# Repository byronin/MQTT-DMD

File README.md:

# MQTT-DMD for ESP8266

## Contents
- PCB [Hardware](https://github.com/byronin/MQTT-DMD/tree/main/Hardware "Hardware") files prepared for controlling the P10 Display.
- [Arduino library](https://github.com/byronin/MQTT-DMD/tree/main/Lib%26Software "Arduino library")  for using P10 Display with Mqtt.

## Sponsor

#### Thanks to PCBWay for handling PCB production.

## Hardware & BOM

  ##### This PCB Desing with Eagle  
  
  ## Schematic

| PCB Components  | Package |Piece || PCB Components  | Package |Piece |  
| ------------- | ------------- |------------- |---------| ------------- | ------------- |------------- |
| ESP8266 Wi-Fi Module  | 12E | 1 pcs  || LM1117-3v3 | SOT-223  | 1 pcs |
| SS14/SS36 Diode  | DO-214AC | 1 pcs || 3v3 Zener Diode  | SOD80C | 1 pcs |
| MAX485-RS485 | SOP 8  | 1 pcs  || 100uf Cap | PANASONIC_D   | 2 pcs |
| 100nf Cap mlcc | 0603  | 3 pcs || 10K Resistor  | 0603  | 8 pcs  |
| 1K Resistor | 0603  | 2 pcs || 120R Resistor  | 0603  | 2 pcs  |
| RED LED  | 0603  | 1 pcs || BLUE LED  | 0603  | 1 pcs  |
| Screw Terminal  | 3.5mm DIP  | 2 pcs  || Header 2x8 FML | 2.54-180  | 1 pcs  |
| Header 1x4 ML  | 2.54-90  | 1 pcs  || Header 1x2 ML  | 2.54-180  | 2 pcs  |
| JUMPER 1x2   | 2.54  | 2 pcs  |  

[You can look BOM.txt for details.](https://github.com/byronin/MQTT-DMD/blob/main/Hardware/BOM.txt "You can look BOM.txt")  

## Test 

#### Shopping List

| Product  | Link |
| ------------- | ------------- |
|P10 Display|[ Link](https://tr.aliexpress.com/item/1005003237909713.html?spm=a2g0o.productlist.0.0.37e759f1OWtOJo&algo_pvid=ac306e69-5e60-4847-98bb-0beb025dface&algo_exp_id=ac306e69-5e60-4847-98bb-0beb025dface-14&pdp_ext_f=%7B%22sku_id%22%3A%2212000024792668676%22%7D&pdp_npi=2%40dis%21TRY%21%21114.7%21%21%21209.95%21%21%402101d8b516565254069212787e109b%2112000024792668676%21sea " Link")|
| LM2596 |[Link](https://tr.aliexpress.com/item/33004374185.html?spm=a2g0o.productlist.0.0.584a4eb1nGv9CS&algo_pvid=40dddc8f-dfae-4d0d-81c2-a52a0aa0245e&algo_exp_id=40dddc8f-dfae-4d0d-81c2-a52a0aa0245e-0&pdp_ext_f=%7B%22sku_id%22%3A%2267088944738%22%7D&pdp_npi=2%40dis%21TRY%21%2113.03%21%21%2126.97%21%21%402101d8b516565255629607266e109b%2167088944738%21sea "Link")|
| Power Jack |[Link](https://tr.aliexpress.com/item/32990462283.html?spm=a2g0o.productlist.0.0.5e2518e2hOOmew&algo_pvid=7db638d6-f6c6-42c6-8043-efdd9c457ccb&algo_exp_id=7db638d6-f6c6-42c6-8043-efdd9c457ccb-17&pdp_ext_f=%7B%22sku_id%22%3A%2266856598002%22%7D&pdp_npi=2%40dis%21TRY%21%2131.28%21%21%21%21%21%402101d8b516565256348121673e109b%2166856598002%21sea "Link")  |
| 12V 3A Power Supply  | [Link](https://tr.aliexpress.com/item/32961533195.html?spm=a2g0o.productlist.0.0.2d7946ffUO6err&algo_pvid=a5d9bf34-bb2b-44ef-beb8-4b2c94ddd551&algo_exp_id=a5d9bf34-bb2b-44ef-beb8-4b2c94ddd551-0&pdp_ext_f=%7B%22sku_id%22%3A%2212000021653748461%22%7D&pdp_npi=2%40dis%21TRY%21%2168.92%21%21%2168.22%21%21%402101d8b516565257067844445e109b%2112000021653748461%21sea "Link")  |

## Software & Library

- The project runs via the [Arduino IDE](https://www.arduino.cc/en/software "Arduino IDE"). If it is not installed, install it.
- Install [ESP8266](https://github.com/esp8266/Arduino "ESP8266") to Arduino.
- Install the [Pubsubclient Lib.](https://github.com/knolleary/pubsubclient "Pubsubclient Lib.") to Arduino.
- Install the [RoninDMD.zip](https://github.com/byronin/MQTT-DMD/blob/main/Lib%26Software/RoninDMD.zip "RoninDMD.zip") with library manager.
- You can connect with any MQTT client application. [MQTTool](https://apps.apple.com/us/app/mqttool/id1085976398 "MQTTool") application and [HiveMQ Public Broker](https://www.hivemq.com/public-mqtt-broker/ "HiveMQ Public Broker") were used in the testing phase of this project. Special thanks [@bjpetit](https://github.com/bjpetit "@bjpetit") .

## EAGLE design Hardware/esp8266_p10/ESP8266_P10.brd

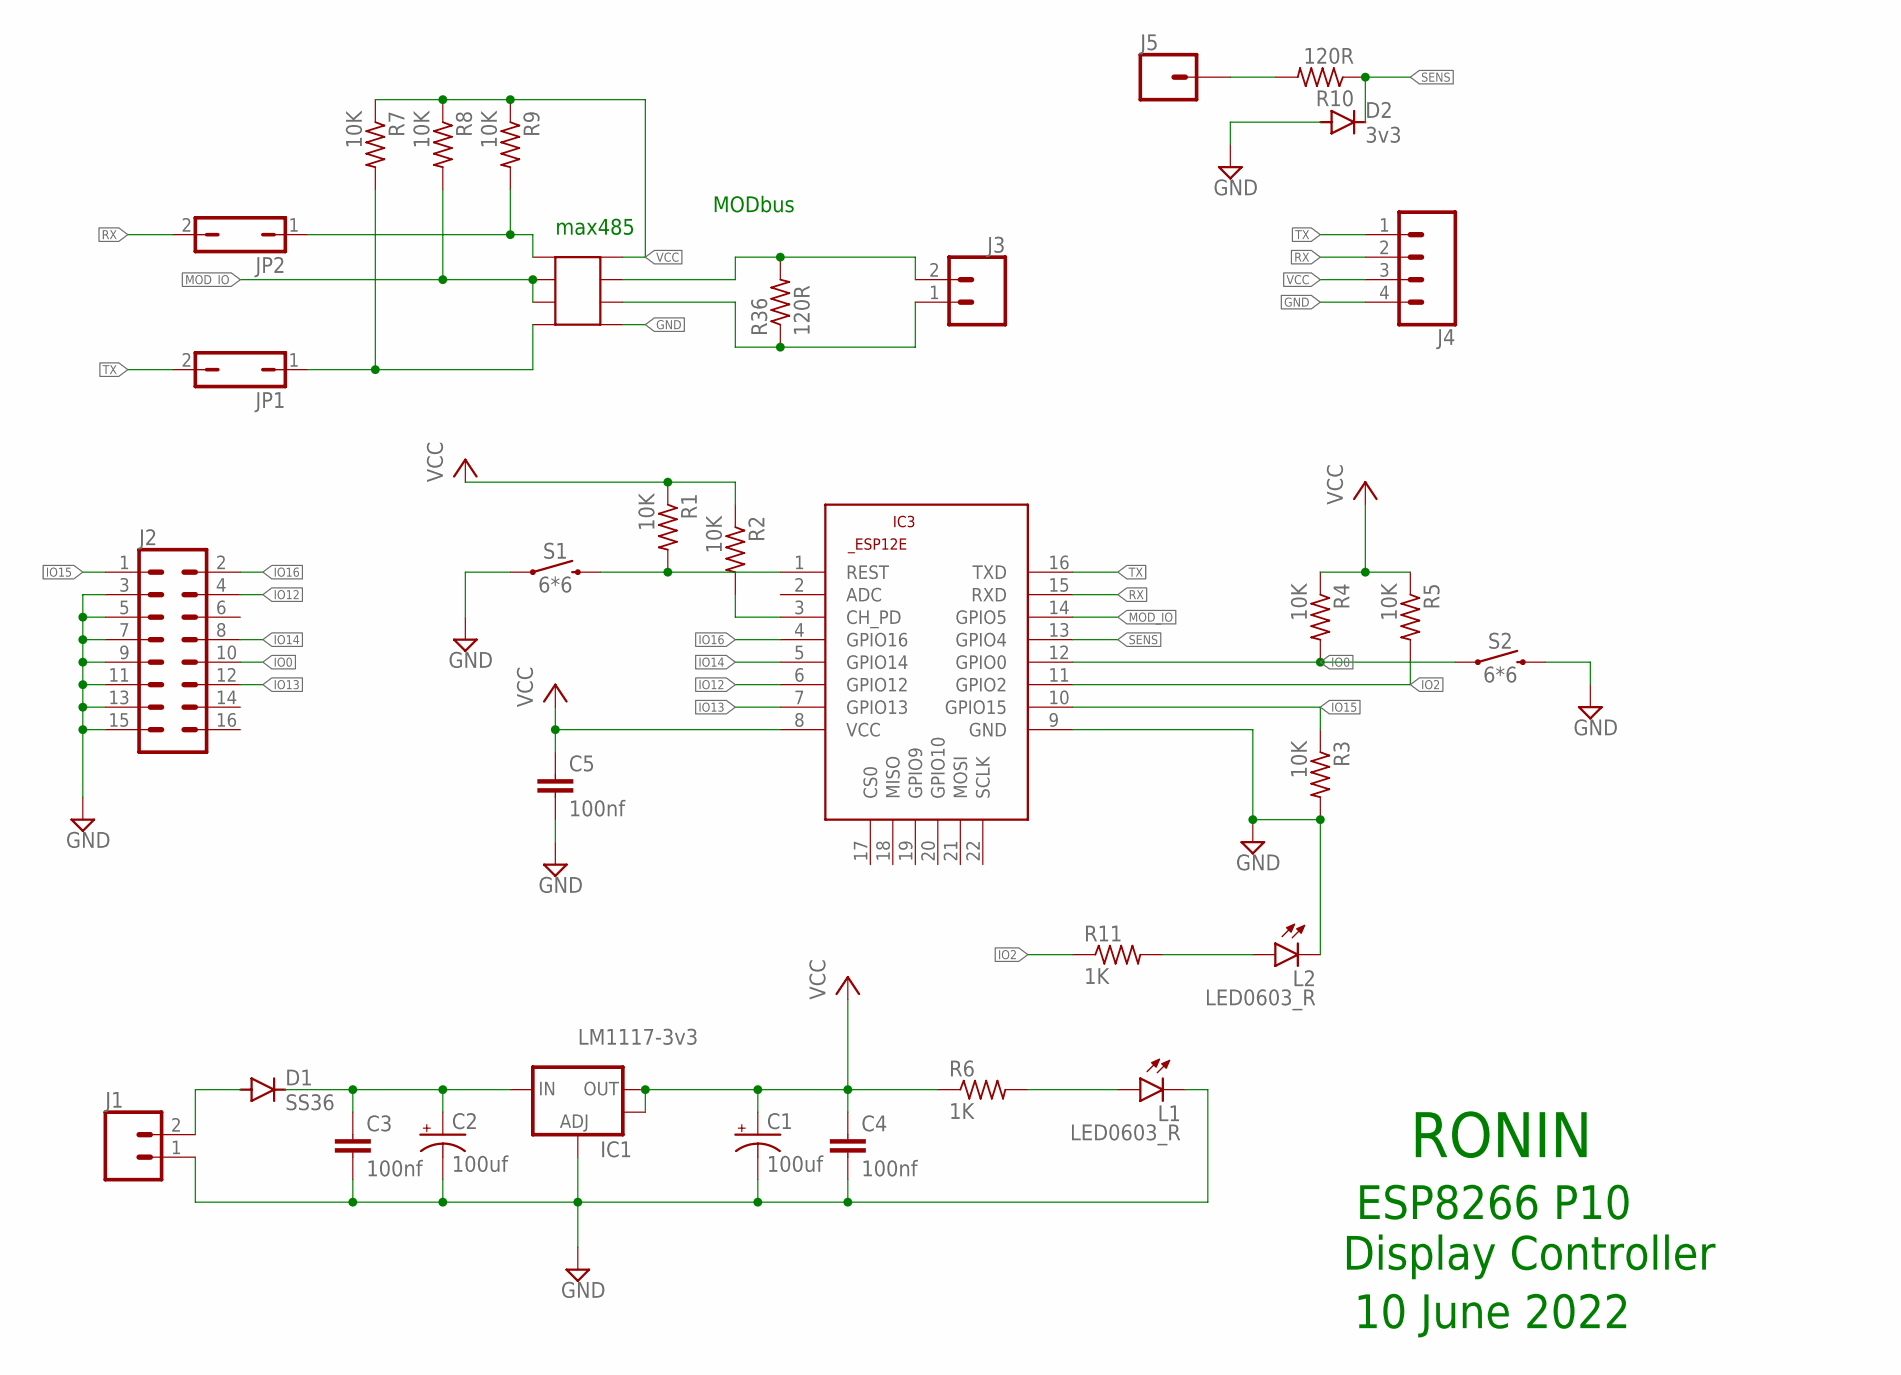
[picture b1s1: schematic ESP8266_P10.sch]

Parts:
C1, C2: 100uf; PANASONIC_D
C3, C4, C5: 100nf; C0603
D1: SS36; DO-214AC
D2: 3v3; SOD80C
IC1: LM1117-3v3; SOT223
IC2: MAX485; HSOP-8
IC3: ESP8266-12EESP12E; ESP8266-ESP12E
J1: CONN_023.5MM; SCREWTERMINAL-3.5MM-2
J2: CONN_08X2; 2X8
J3: CONN_023.5MM-NO_SILK; SCREWTERMINAL-3.5MM-2-NS
J4: CONN_04; 1X04
J5: CONN_01; 1X01
JP1, JP2: JP1Q; JP1
L1, L2: LED0603_R; 0603_LED_GREEN
R1, R2, R3, R4, R5, R7, R8, R9: 10K; R0603
R6, R11: 1K; R0603
R10, R36: 120R; R0603
S1, S2: 6*6; TACTILE_SWITCH_PTH_6.0MM

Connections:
CV: IC2.4, JP1.1, R7.2
FV: IC2.1, JP2.1, R9.2
GND: C1.-, C2.-, C3.2, C4.2, C5.2, D2.A, IC1.1 (ADJ), IC2.5, IC3.9 (GND), J1.1, J2.3, J2.5, J2.7, J2.9, J2.11, J2.13, J2.15, J4.4, L1.C, L2.C, R3.2, S1.1, S2.3 (2)
IO0: IC3.12 (GPIO0), J2.10, R4.2, S2.1
IO2: IC3.11 (GPIO2), R5.2, R11.1
IO12: IC3.6 (GPIO12), J2.4
IO13: IC3.7 (GPIO13), J2.12
IO14: IC3.5 (GPIO14), J2.8
IO15: IC3.10 (GPIO15), J2.1, R3.1
IO16: IC3.4 (GPIO16), J2.2
MOD_IO: IC2.2, IC2.3, IC3.14 (GPIO5), R8.2
unnamed: IC3.1 (REST), R1.2, S1.3 (2)
unnamed: IC3.3 (CH_PD), R2.2
unnamed: C2.+, C3.1, D1.C, IC1.3 (IN)
unnamed: L1.A, R6.2
unnamed: J5.1, R10.2
unnamed: L2.A, R11.2
unnamed: D1.A, J1.2
unnamed: IC2.7, J3.2, R36.2
unnamed: IC2.6, J3.1, R36.1
RX: IC3.15 (RXD), J4.2, JP2.2
SENS: D2.C, IC3.13 (GPIO4), R10.1
TX: IC3.16 (TXD), J4.1, JP1.2
VCC: C1.+, C4.1, C5.1, IC1.2 (OUT), IC1.4 (OUT), IC2.8, IC3.8 (VCC), J4.3, R1.1, R2.1, R4.1, R5.1, R6.1, R7.1, R8.1, R9.1

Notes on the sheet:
RONIN
ESP8266 P10 Display Controller
10 June 2022
MODbus
max485

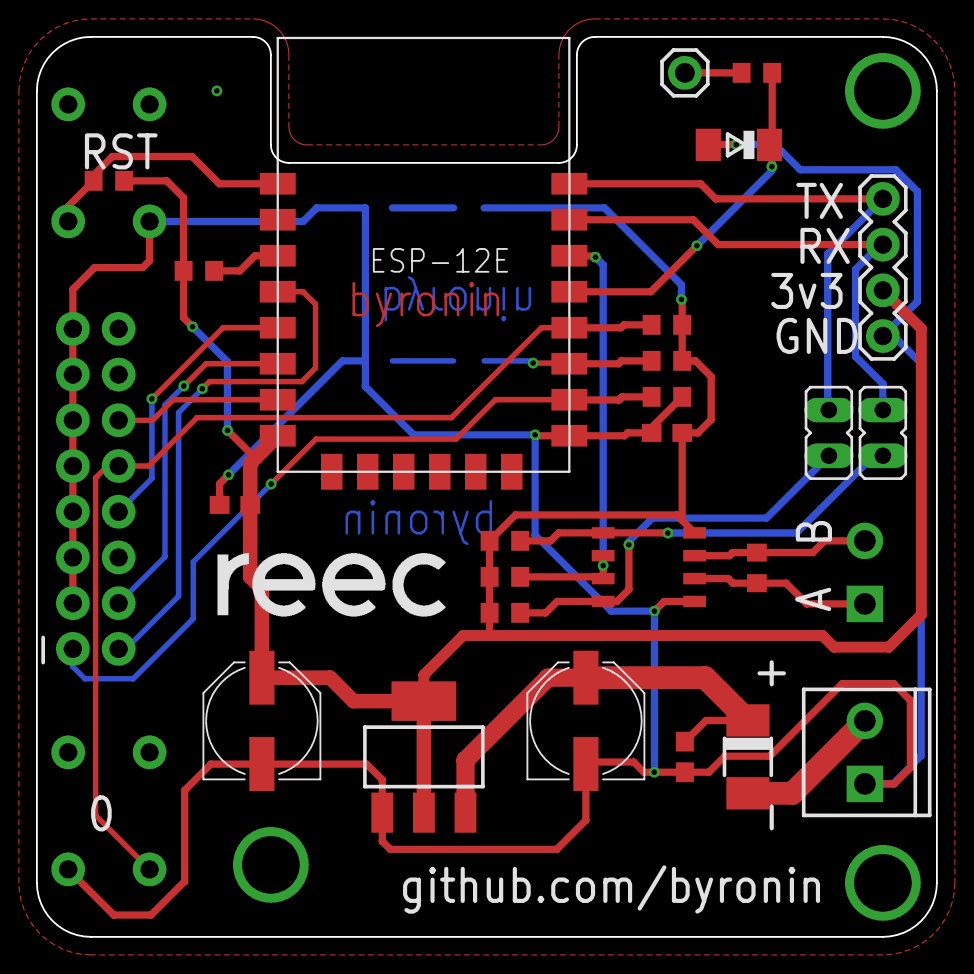
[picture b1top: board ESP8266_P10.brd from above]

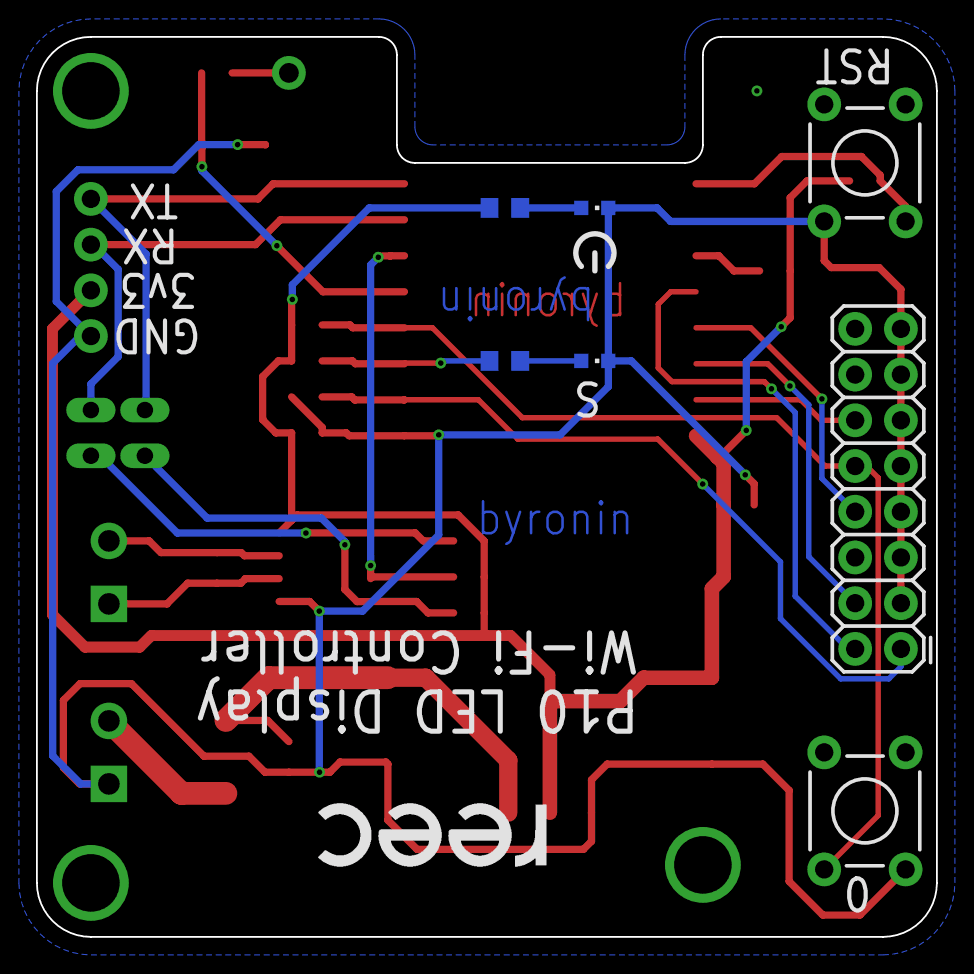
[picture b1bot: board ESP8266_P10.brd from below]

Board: 2 copper layers, 50.0 x 50.0 mm, 33 parts (7 on the bottom side), 24 nets.

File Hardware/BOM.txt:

Partlist exported from C:/Users/Abdullah/Desktop/youtube/ESP8266_P10/Hardware/esp8266_p10/ESP8266_P10.sch at 12.06.2022 16:16

Part Value      Device                          Package                  Description                                                                                                      POPULARITY PROD_ID     SF_SKU   
C1   100uf      CAPACITOR_POLD                  PANASONIC_D                                                                                                                                                               
C2   100uf      CAPACITOR_POLD                  PANASONIC_D                                                                                                                                                               
C3   100nf      CAPACITOR_CER4                  C0603                                                                                                                                                                     
C4   100nf      CAPACITOR_CER4                  C0603                                                                                                                                                                     
C5   100nf      CAPACITOR_CER4                  C0603                                                                                                                                                                     
D1   SS36       DIODEAC2                        DO-214AC                                                                                                                                                                  
D2   3v3        DIODE80C                        SOD80C                                                                                                                                                                    
IC1  LM1117-3v3 V_REG_LM1117SOT223              SOT223                   Voltage Regulator LM1117                                                                                                                         
IC2  MAX485     SOP_8                           HSOP-8                                                                                                                                                                    
IC3             ESP8266-12EESP12E               ESP8266-ESP12E           ESP8266-12E Library for Eagle CAD                                                                                                                
J1              CONN_023.5MM                    SCREWTERMINAL-3.5MM-2    Multi connection point. Often used as Generic Header-pin footprint for 0.1 inch spaced/style header connections             CONN-08399           
J2              CONN_08X2                       2X8                      Multi connection point. Often used as Generic Header-pin footprint for 0.1 inch spaced/style header connections                                  
J3              CONN_023.5MM-NO_SILK            SCREWTERMINAL-3.5MM-2-NS Multi connection point. Often used as Generic Header-pin footprint for 0.1 inch spaced/style header connections             CONN-08399           
J4              CONN_04                         1X04                     Multi connection point. Often used as Generic Header-pin footprint for 0.1 inch spaced/style header connections             CONN-09696           
J5              CONN_01                         1X01                     Single connection point. Often used as Generic Header-pin footprint for 0.1 inch spaced/style header connections                                 
JP1             JP1Q                            JP1                      JUMPER                                                                                                           15                              
JP2             JP1Q                            JP1                      JUMPER                                                                                                           15                              
L1   LED0603_R  LED0603_R                       0603_LED_GREEN                                                                                                                                                            
L2   LED0603_R  LED0603_R                       0603_LED_GREEN                                                                                                                                                            
R1   10K        RESISTOR0603                    R0603                                                                                                                                                                     
R2   10K        RESISTOR0603                    R0603                                                                                                                                                                     
R3   10K        RESISTOR0603                    R0603                                                                                                                                                                     
R4   10K        RESISTOR0603                    R0603                                                                                                                                                                     
R5   10K        RESISTOR0603                    R0603                                                                                                                                                                     
R6   1K         RESISTOR0603                    R0603                                                                                                                                                                     
R7   10K        RESISTOR0603                    R0603                                                                                                                                                                     
R8   10K        RESISTOR0603                    R0603                                                                                                                                                                     
R9   10K        RESISTOR0603                    R0603                                                                                                                                                                     
R10  120R       RESISTOR0603                    R0603                                                                                                                                                                     
R11  1K         RESISTOR0603                    R0603                                                                                                                                                                     
R36  120R       RESISTOR0603                    R0603                                                                                                                                                                     
S1   6*6        MOMENTARY-SWITCH-SPST-PTH-6.0MM TACTILE_SWITCH_PTH_6.0MM Momentary Switch (Pushbutton) - SPST                                                                                         SWCH-08441 COM-00097
S2   6*6        MOMENTARY-SWITCH-SPST-PTH-6.0MM TACTILE_SWITCH_PTH_6.0MM Momentary Switch (Pushbutton) - SPST                                                                                         SWCH-08441 COM-00097

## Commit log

2022-06-29 repo_change
2022-06-29 Jpg small
2022-06-29 img small
2022-07-02 defat

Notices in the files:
parts and their libraries:
SparkFun-Connectors: Licensing: Creative Commons ShareAlike 4.0 International - https://creativecommons.org/licenses/by-sa/4.0
